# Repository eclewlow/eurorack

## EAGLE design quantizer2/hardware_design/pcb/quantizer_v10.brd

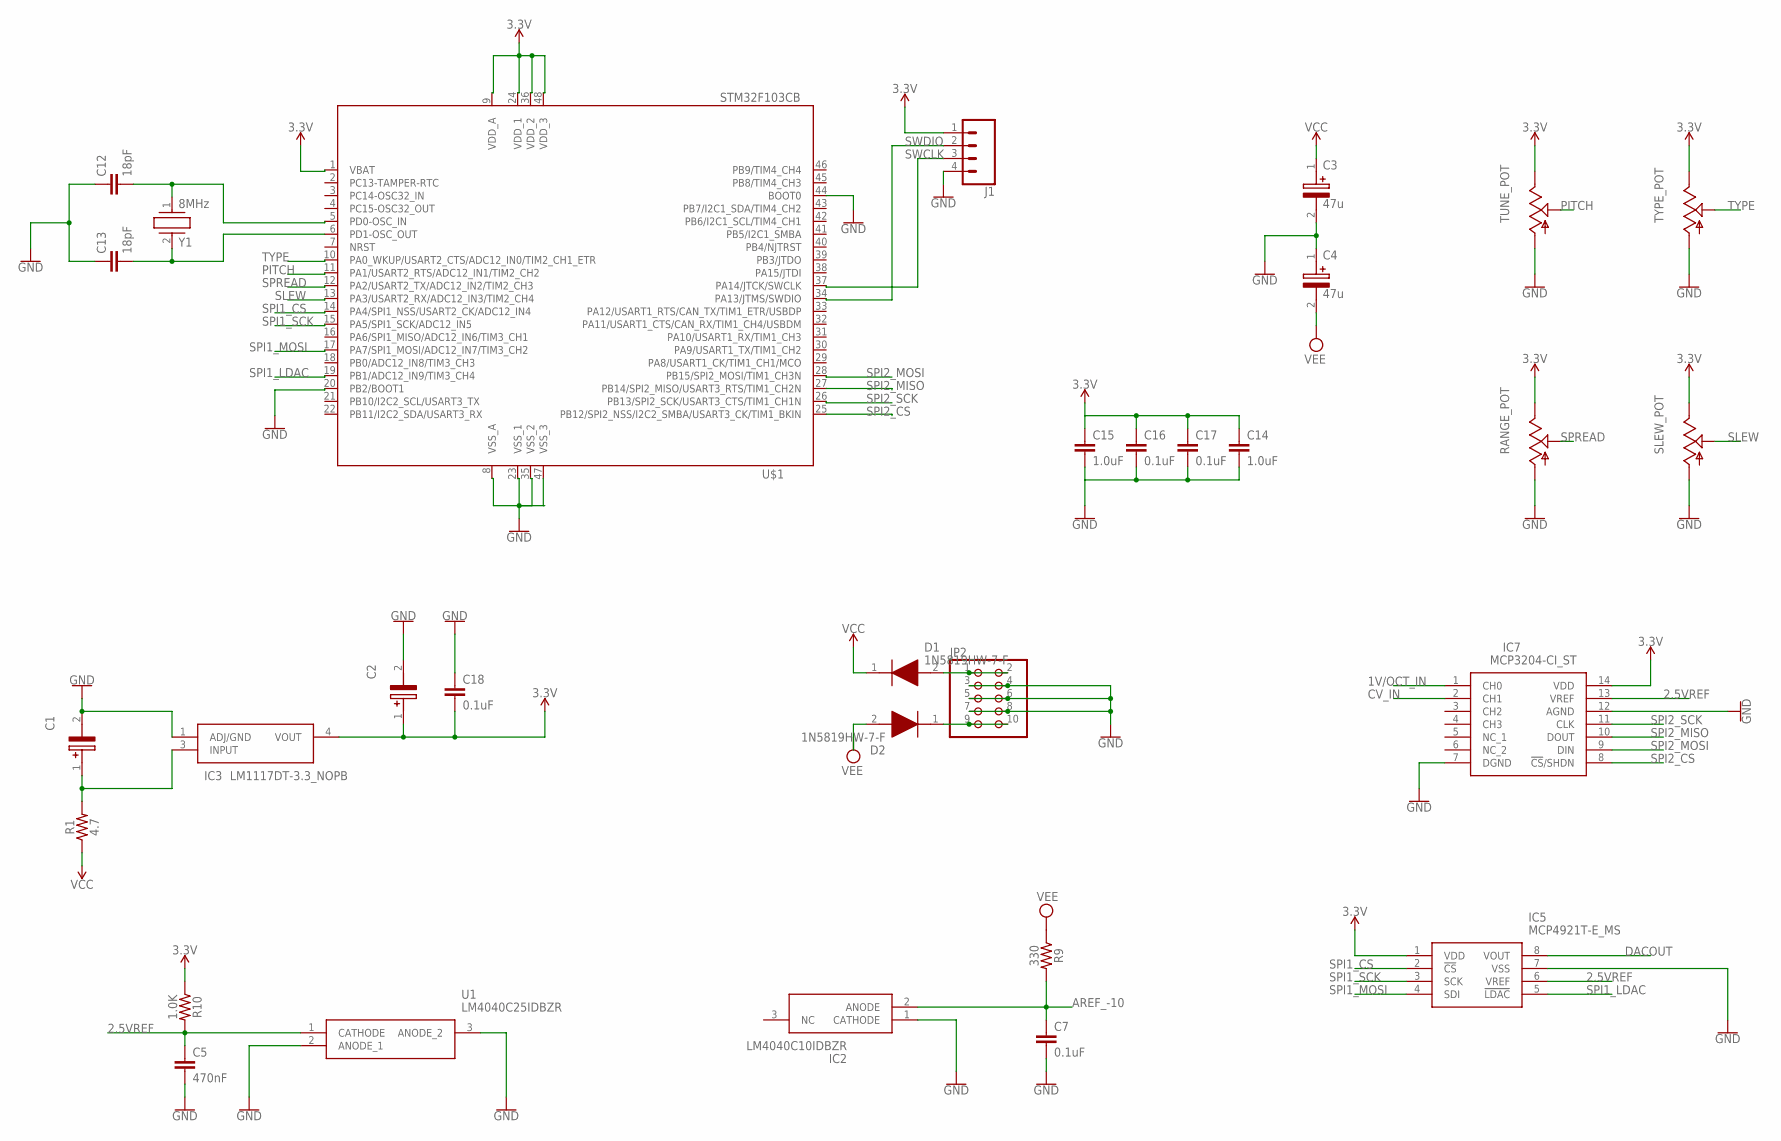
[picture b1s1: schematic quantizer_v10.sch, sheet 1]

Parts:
C1, C2: 22uF; EEE0GA101SR
C3, C4: 47u; EEE1AA101SP
C5: 470nF; 0603
C7, C16, C17, C18: 0.1uF; 0603
C12, C13: 18pF; 0603
C14, C15: 1.0uF; 0603
D1, D2: 1N5819HW-7-F; SOD3716X145N
IC2: LM4040C10IDBZR; SOT95P237X112-3N
IC3: LM1117DT-3.3_NOPB; TO228P991X238-3N
IC5: MCP4921T-E_MS; SOP65P490X110-8N
IC7: MCP3204-CI_ST; SOP65P640X120-14N
J1: CONN_04; 1X04
JP2: PINHD-2X5; 2X05
R1: 4.7; 1206
R9: 330; 0603
R10: 1.0K; 0603
RANGE_POT: POT_USVERTICAL_PS; ALPS_POT_VERTICAL_PS
SLEW_POT: POTENTIOMETER-ALPHA-9MM_VERTICAL_; POTENTIOMETER-ALPHA-9MM_VERTICAL
TUNE_POT: POT_USVERTICAL_PS; ALPS_POT_VERTICAL_PS
TYPE_POT: POT_USVERTICAL_PS; ALPS_POT_VERTICAL_PS
U1: LM4040C25IDBZR; SOT95P237X112-3N
U$1: STM32F103CB; LQFP48
Y1: 8MHz; ABLS

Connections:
1V/OCT_IN: IC7.1 (CH0); also elsewhere on the board
2.5VREF: C5.1, IC5.6 (VREF), IC7.13 (VREF), R10.2, U1.1 (CATHODE)
3.3V: C2.1 (+), C18.2, IC3.4 (VOUT), IC5.1 (VDD), IC7.14 (VDD), J1.1, R10.1, RANGE_POT.P$1 (E), SLEW_POT.3 (E), TUNE_POT.P$1 (E), TYPE_POT.P$1 (E), U$1.1 (VBAT), U$1.9 (VDD_A), U$1.24 (VDD_1), U$1.36 (VDD_2), U$1.48 (VDD_3)
AREF_-10: C7.1, IC2.2 (ANODE), R9.2; also elsewhere on the board
CV_IN: IC7.2 (CH1); also elsewhere on the board
DACOUT: IC5.8 (VOUT); also elsewhere on the board
GND: C1.2 (-), C2.2 (-), C3.2 (-), C4.1 (+), C5.2, C7.2, C12.1, C13.1, C18.1, IC2.1 (CATHODE), IC3.1 (ADJ/GND), IC5.7 (VSS), IC7.7 (DGND), IC7.12 (AGND), J1.4, JP2.3, JP2.4, JP2.5, JP2.6, JP2.7, JP2.8, RANGE_POT.P$3 (A), SLEW_POT.1 (A), TUNE_POT.P$3 (A), TYPE_POT.P$3 (A), U1.2 (ANODE_1), U1.3 (ANODE_2), U$1.8 (VSS_A), U$1.20 (PB2/BOOT1), U$1.23 (VSS_1), U$1.35 (VSS_2), U$1.44 (BOOT0), U$1.47 (VSS_3); also elsewhere on the board
unnamed: C1.1 (+), IC3.3 (INPUT), R1.2
unnamed: D1.2 (A), JP2.1, JP2.2
unnamed: D2.1 (K), JP2.9, JP2.10
unnamed: C12.2, U$1.5 (PD0-OSC_IN), Y1.1
unnamed: C13.2, U$1.6 (PD1-OSC_OUT), Y1.2
unnamed: C14.1, C15.1, C16.1, C17.1
unnamed: C14.2, C15.2, C16.2, C17.2
PITCH: TUNE_POT.P$2 (S), U$1.11 (PA1/USART2_RTS/ADC12_IN1/TIM2_CH2)
SLEW: SLEW_POT.2 (S), U$1.13 (PA3/USART2_RX/ADC12_IN3/TIM2_CH4)
SPI1_CS: IC5.2 (!CS), U$1.14 (PA4/SPI1_NSS/USART2_CK/ADC12_IN4)
SPI1_LDAC: IC5.5 (!LDAC), U$1.19 (PB1/ADC12_IN9/TIM3_CH4)
SPI1_MOSI: IC5.4 (SDI), U$1.17 (PA7/SPI1_MOSI/ADC12_IN7/TIM3_CH2)
SPI1_SCK: IC5.3 (SCK), U$1.15 (PA5/SPI1_SCK/ADC12_IN5)
SPI2_CS: IC7.8 (!CS!/SHDN), U$1.25 (PB12/SPI2_NSS/I2C2_SMBA/USART3_CK/TIM1_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)
SPI2_MISO: IC7.10 (DOUT), U$1.27 (PB14/SPI2_MISO/USART3_RTS/TIM1_CH2N)
SPI2_MOSI: IC7.9 (DIN), U$1.28 (PB15/SPI2_MOSI/TIM1_CH3N)
SPI2_SCK: IC7.11 (CLK), U$1.26 (PB13/SPI2_SCK/USART3_CTS/TIM1_CH1N)
SPREAD: RANGE_POT.P$2 (S), U$1.12 (PA2/USART2_TX/ADC12_IN2/TIM2_CH3)
SWCLK: J1.3, U$1.37 (PA14/JTCK/SWCLK)
SWDIO: J1.2, U$1.34 (PA13/JTMS/SWDIO)
TYPE: TYPE_POT.P$2 (S), U$1.10 (PA0_WKUP/USART2_CTS/ADC12_IN0/TIM2_CH1_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)
VCC: C3.1 (+), D1.1 (K), R1.1; also elsewhere on the board
VEE: C4.2 (-), D2.2 (A), R9.1; also elsewhere on the board

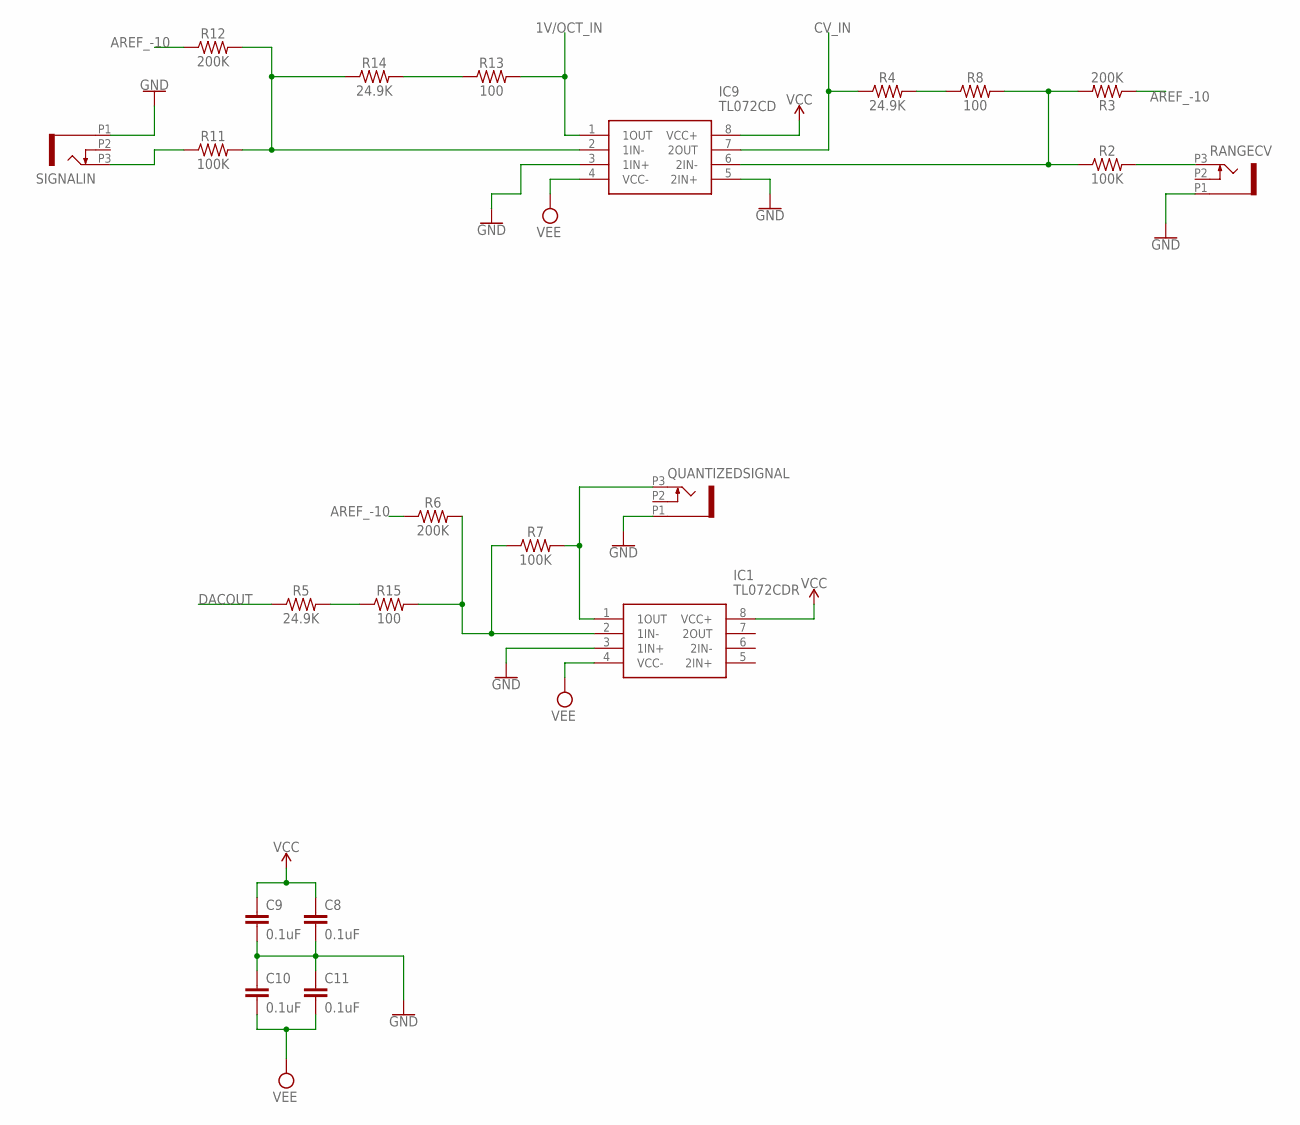
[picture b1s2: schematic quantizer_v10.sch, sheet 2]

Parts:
C8, C9, C10, C11: 0.1uF; 0603
IC1: TL072CDR; SOIC127P600X175-8N
IC9: TL072CD; SOIC127P600X175-8N
QUANTIZEDSIGNAL: PJ301_THONKICONN6; WQP_PJ_301M6
R2, R7, R11: 100K; 0603
R3, R6, R12: 200K; 0603
R4, R5, R14: 24.9K; 0603
R8, R13, R15: 100; 0603
RANGECV: PJ301_THONKICONN6; WQP_PJ_301M6
SIGNALIN: PJ301_THONKICONN6; WQP_PJ_301M6

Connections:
1V/OCT_IN: IC9.1 (1OUT), R13.2; also elsewhere on the board
AREF_-10: R3.1, R6.1, R12.1; also elsewhere on the board
CV_IN: IC9.7 (2OUT), R4.1; also elsewhere on the board
DACOUT: R5.1; also elsewhere on the board
GND: C8.2, C9.2, C10.1, C11.1, IC1.3 (1IN+), IC9.3 (1IN+), IC9.5 (2IN+), QUANTIZEDSIGNAL.P1 (1), RANGECV.P1 (1), SIGNALIN.P1 (1); also elsewhere on the board
unnamed: R4.2, R8.1
unnamed: R11.1, SIGNALIN.P3 (3)
unnamed: IC9.6 (2IN-), R2.1, R3.2, R8.2
unnamed: IC9.2 (1IN-), R11.2, R12.2, R14.1
unnamed: R2.2, RANGECV.P3 (3)
unnamed: IC1.1 (1OUT), QUANTIZEDSIGNAL.P3 (3), R7.2
unnamed: R13.1, R14.2
unnamed: R5.2, R15.1
unnamed: IC1.2 (1IN-), R6.2, R7.1, R15.2
VCC: C8.1, C9.1, IC1.8 (VCC+), IC9.8 (VCC+); also elsewhere on the board
VEE: C10.2, C11.2, IC1.4 (VCC-), IC9.4 (VCC-); also elsewhere on the board

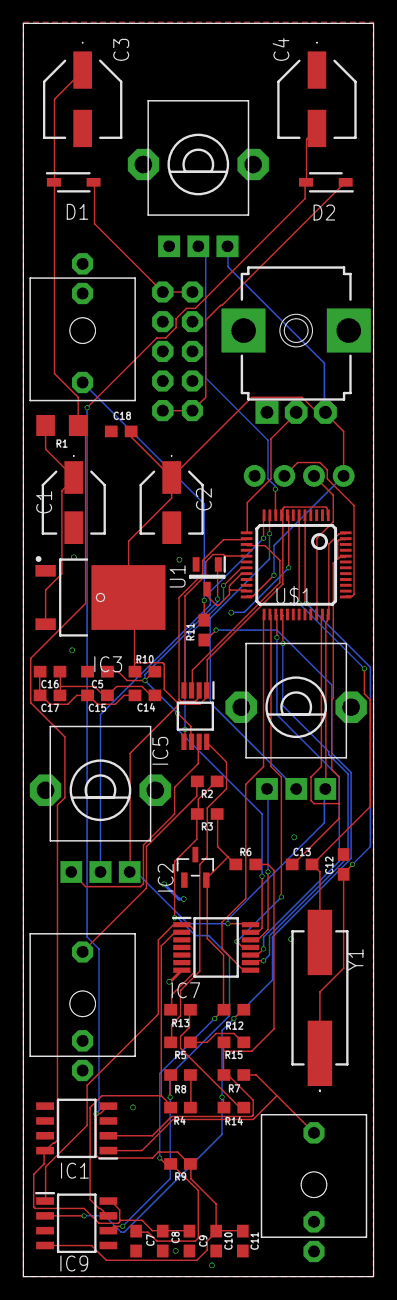
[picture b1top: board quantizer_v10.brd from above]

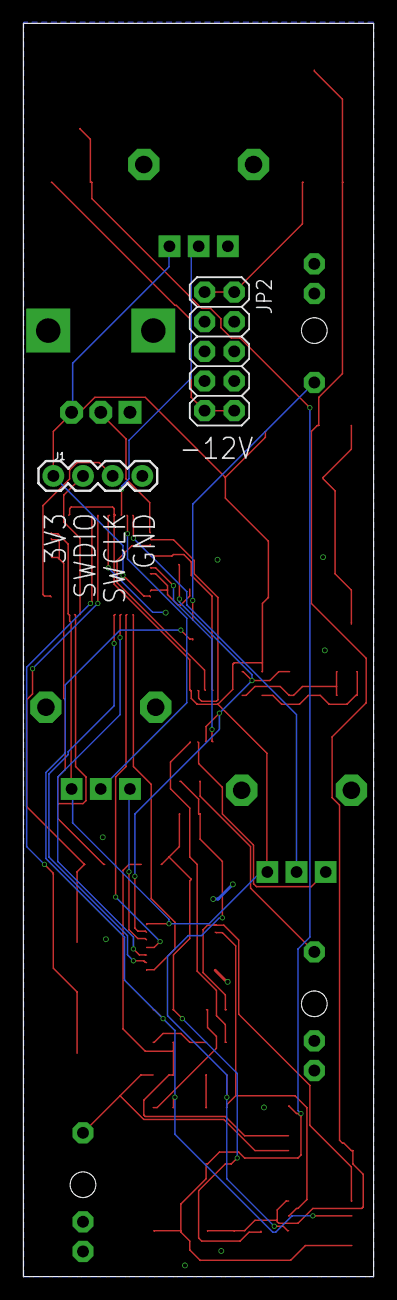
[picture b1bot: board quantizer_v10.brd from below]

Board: 2 copper layers, 30.0 x 107.3 mm, 52 parts (2 on the bottom side), 39 nets.

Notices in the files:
parts and their libraries:
SparkFun-Connectors: Licensing: Creative Commons ShareAlike 4.0 International - https://creativecommons.org/licenses/by-sa/4.0
